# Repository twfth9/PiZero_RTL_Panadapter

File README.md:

# PiZero_RTL_Panadapter
Rasp Pi Zero, RTLSDR-based panadapter module

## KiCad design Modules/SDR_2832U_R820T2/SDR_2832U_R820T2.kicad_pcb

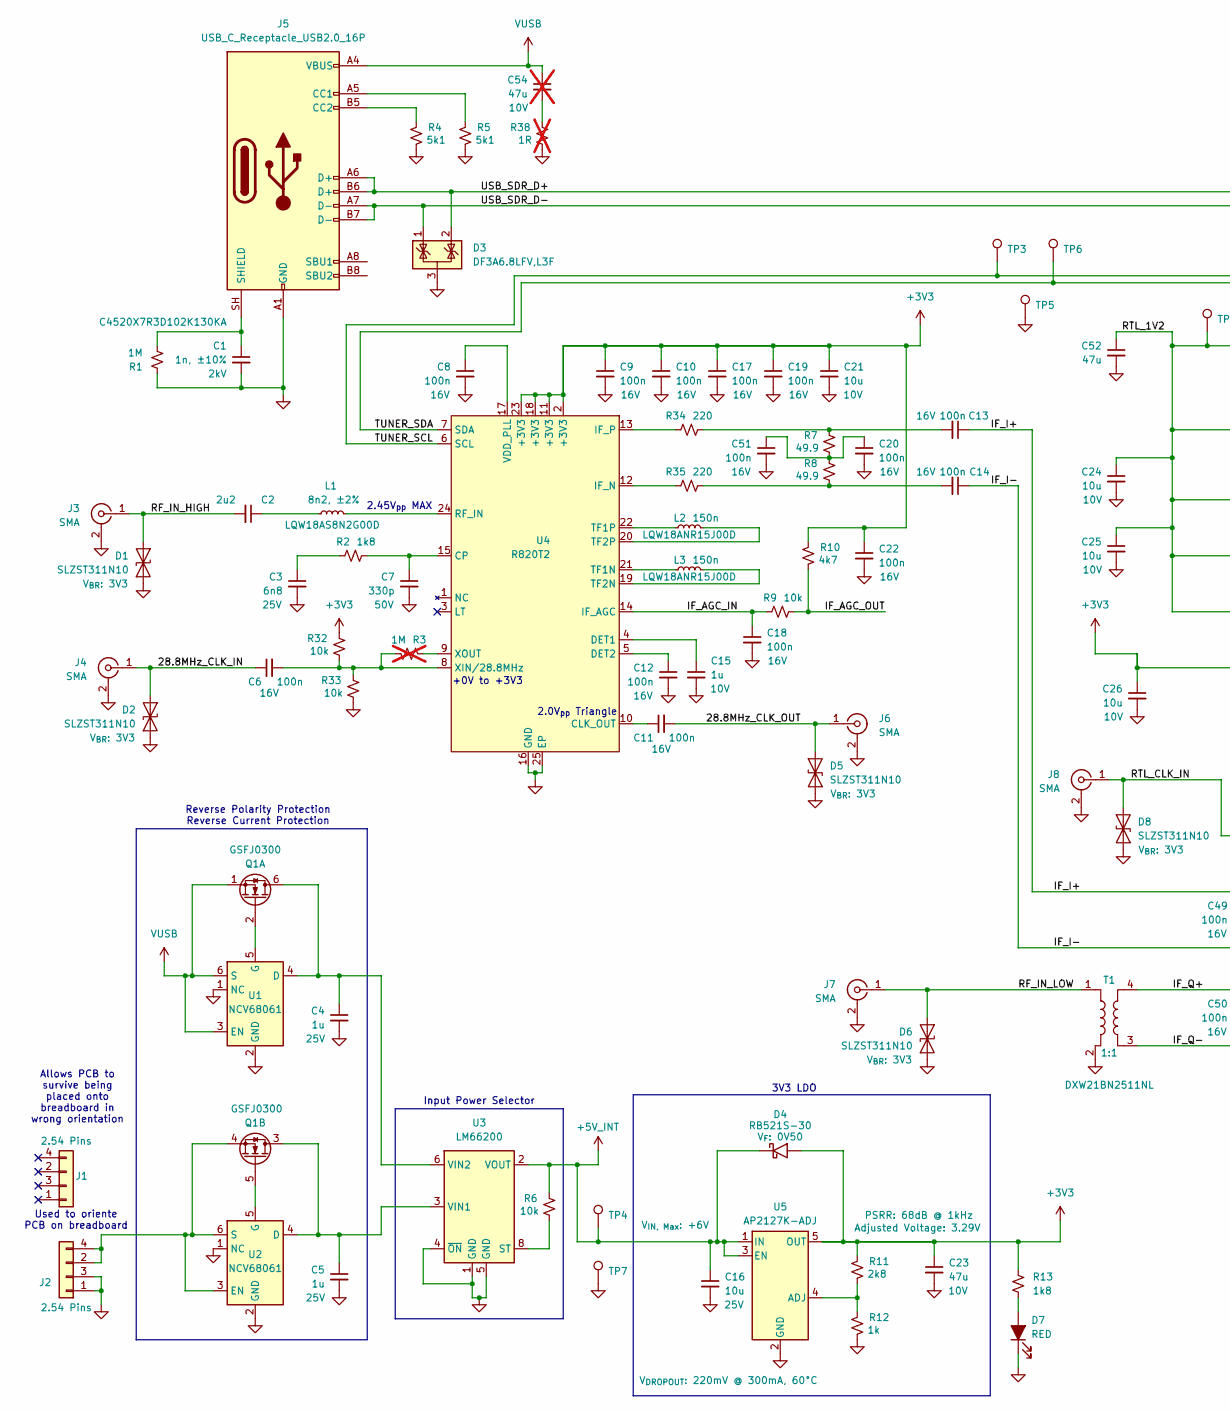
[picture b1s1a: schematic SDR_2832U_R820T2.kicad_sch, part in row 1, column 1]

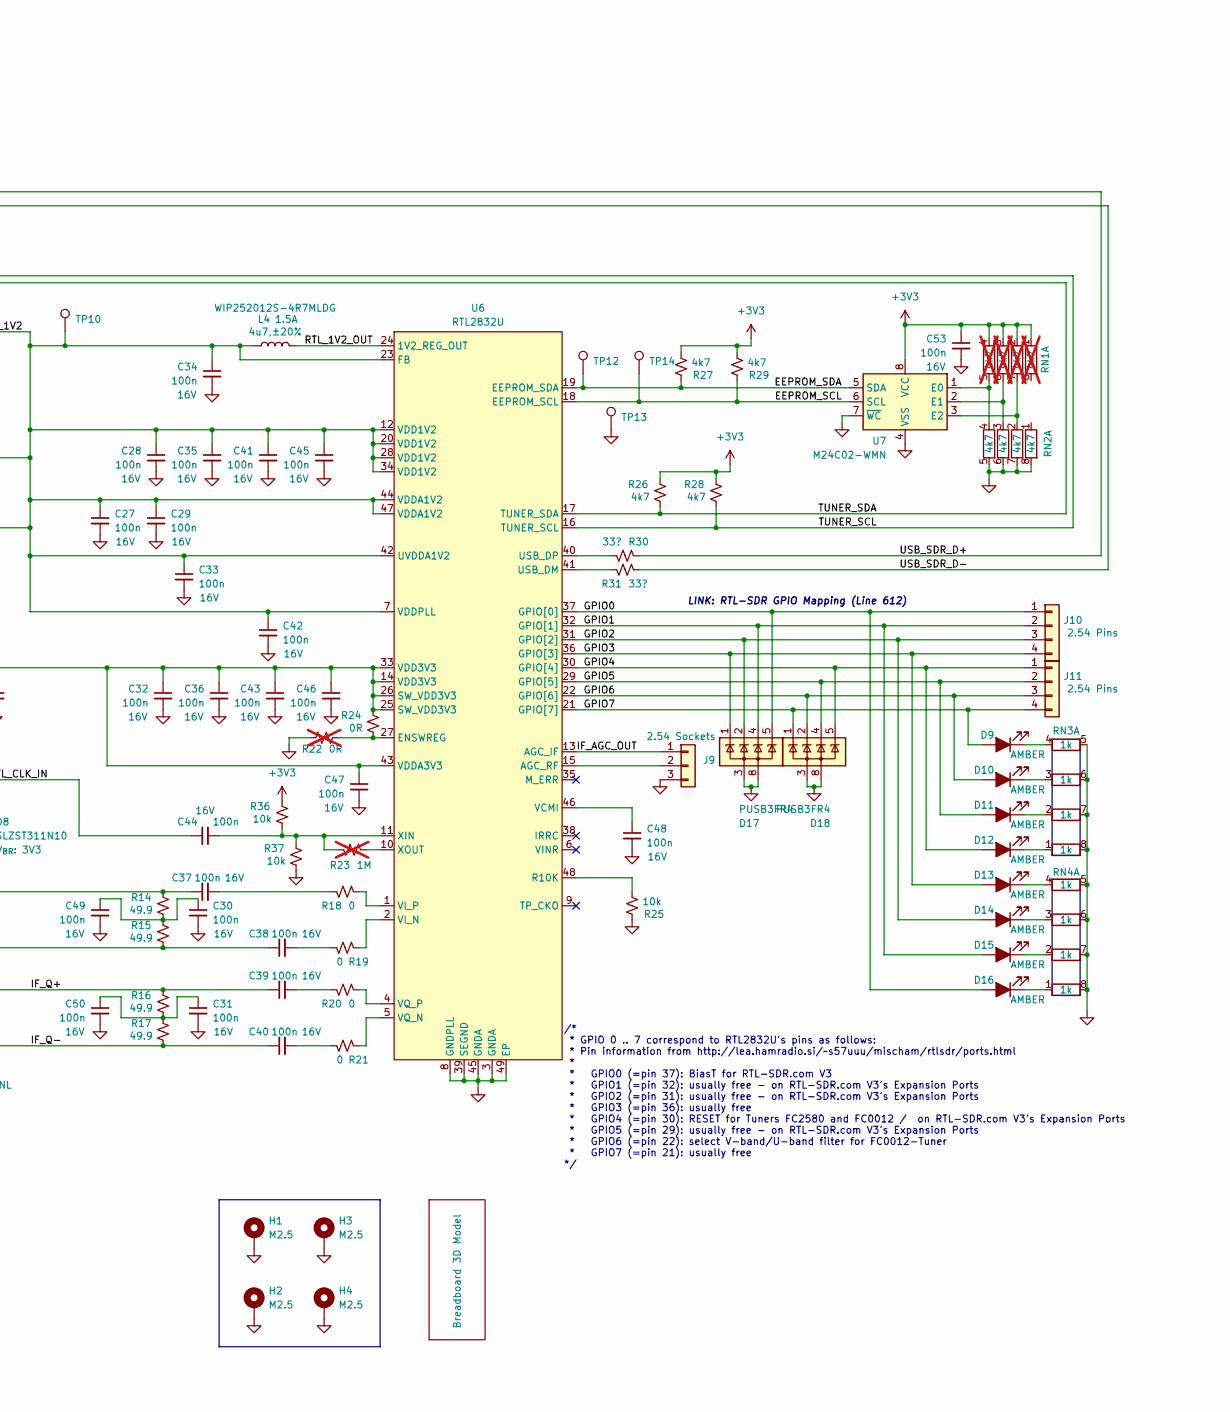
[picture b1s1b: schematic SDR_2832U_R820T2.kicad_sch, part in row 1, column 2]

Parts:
C1: 1n, ±10%; C_1808_4520Metric; Voltage 2kV; Part Number C4520X7R3D102K130KA; DigiKey 445-2386-1-ND
C2: 2u2; Worthington_C_Narrow_0402_0603; Voltage 10V
C3: 6n8; Worthington_C_Narrow_0201; Voltage 25V; Manufacturer Part Number GMC02X5R682K25NT; DigiKey 4713-GMC02X5R682K25NTCT-ND
C4, C5: 1u; Worthington_C_Narrow_0402; Voltage 25V; Manufacturer Part Number GMC04X5R106M10NT; DigiKey 4713-GMC04X5R106M10NTCT-ND
C6, C8, C9, C10, C11, C12, C13, C14, C17, C18, C19, C20, C22, C27, C28, C29, C30, C31, C32, C33, C34, C35, C36, C37, C38, C39, C40, C41, C42, C43, C44, C45, C46, C47, C48, C49, C50, C51, C53: 100n; Worthington_C_Narrow_0201; Voltage 16V; Manufacturer Part Number C0603X6S1C104K030BC; DigiKey 445-15903-1-ND
C7: 330p; Worthington_C_Narrow_0201; Voltage 50V; Manufacturer Part Number GMC02X7R331J50NT; DigiKey 4713-GMC02X7R331J50NTCT-ND
C15: 1u; Worthington_C_Narrow_0201; Voltage 10V; Manufacturer Part Number GMC02X5R105K10NT; DigiKey 4713-GMC02X5R105K10NTCT-ND
C16: 10u; Worthington_C_Narrow_0402; Voltage 25V; Manufacturer Part Number GMC04X5R106M10NT; DigiKey 4713-GMC04X5R106M10NTCT-ND
C21, C24, C25, C26: 10u; Worthington_C_Narrow_0402; Voltage 10V; Manufacturer Part Number GMC04X5R106M10NT; DigiKey 4713-GMC04X5R106M10NTCT-ND
C23: 47u; Worthington_C_0805; Voltage 10V; Manufacturer Part Number GMC04X5R106M10NT; DigiKey 4713-GMC04X5R106M10NTCT-ND
C52: 47u; Worthington_C_Narrow_0603
C54: 47u; Worthington_C_0805; Voltage 10V; Manufacturer Part Number GMC04X5R106M10NT; DigiKey 4713-GMC04X5R106M10NTCT-ND; not fitted
D1, D2, D5, D6, D8: SLZST311N10; D_SOD-882; Part Number SLZST311N10; DigiKey 5399-SLZST311N10CT-ND
D3: DF3A6.8LFV,L3F; SOT-723
D4: RB521S-30; D_SOD-523; Part Number RB521S-30; DigiKey 5399-RB521S-30CT-ND
D7: RED; Worthington_LED_0402
D9, D10, D11, D12, D13, D14, D15, D16: AMBER; Worthington_LED_0402
D17, D18: PUSB3FR4; Diodes_UDFN-10_1x2.5mm_P0.5mm
H1, H2, H3, H4: M2.5; MountingHole_2.7mm_M2.5_ISO7380_Pad
J1, J2: 2.54 Pins; PinHeader_2x02_P2.54mm_Vertical
J3, J4, J6, J7, J8: SMA; SMA_Amphenol_132289_EdgeMount
J5: USB_C_Receptacle_USB2.0_16P; USB_C_Receptacle_GCT_USB4105-xx-A_16P_TopMnt_Horizontal
J9: 2.54 Sockets; PinHeader_1x03_P2.54mm_Vertical
J10, J11: 2.54 Pins; PinHeader_1x04_P2.54mm_Vertical
L1: 8n2, ±2%; Worthington_L_Narrow_0603_RF; Manufacturer Part Number LQW18AS8N2G00D; DigiKey 490-LQW18AS8N2G00DCT-ND
L2, L3: 150n; Worthington_L_Narrow_0603_RF; Manufacturer Part Number LQW18ANR15J00D; DigiKey 490-6924-1-ND
L4: 4u7,±20%; L_1008_2520Metric; Manufacturer Part Number WIP252012S-4R7MLDG; DigiKey 3526-WIP252012S-4R7MLDGCT-ND
Q1: GSFJ0300; SOT-563; Part Number GSFJ0300; DigiKey 4786-GSFJ0300CT-ND
R1: 1M; Worthington_R_Narrow_0201
R2, R13: 1k8; Worthington_R_Narrow_0201
R3, R23: 1M; Worthington_R_Narrow_0201; not fitted
R4, R5: 5k1; Worthington_R_Narrow_0201
R6, R9, R25, R32, R33, R36, R37: 10k; Worthington_R_Narrow_0201
R7, R8, R14, R15, R16, R17: 49.9; Worthington_R_Narrow_0201
R10, R26, R27, R28, R29: 4k7; Worthington_R_Narrow_0201
R11: 2k8; Worthington_R_Narrow_0201
R12: 1k; Worthington_R_Narrow_0201
R18, R19, R20, R21: 0; Worthington_R_Narrow_0201
R22: 0R; Worthington_R_Narrow_0201; not fitted
R24: 0R; Worthington_R_Narrow_0201
R30, R31: 33?; Worthington_R_Narrow_0201
R34, R35: 220; Worthington_R_Narrow_0201
R38: 1R; R_0805_2012Metric; not fitted
RN1: 4k7; RESCAXE80P320X160X70-8N; DigiKey Part CAT16-4702F4LFCT-ND; not fitted
RN2: 4k7; RESCAXE80P320X160X70-8N; DigiKey Part CAT16-4702F4LFCT-ND
RN3, RN4: 1k; RESCAXE80P320X160X70-8N; DigiKey Part CAT16-4702F4LFCT-ND
S1: Breadboard 3D Model; Breadboard_400
T1: DXW21BN2511NL; XFMR_ATB2012-50011-T000
TP3, TP4, TP5, TP6, TP7, TP10, TP12, TP13, TP14: TestPoint; TestPoint_Keystone_5000-5004_Miniature
U1, U2: NCV68061; TSOP-6_1.65x3.05mm_P0.95mm; DigiKey 488-NCV68061SNAIT1GCT-ND
U3: LM66200; SOT-583-8
U4: R820T2; QFN-24-1EP_4x4mm_P0.5mm_EP2.15x2.15mm_ThermalVias
U5: AP2127K-ADJ; SOT-23-5; Adjusted Voltage 3.29V; Part Number AP2127K-ADJTRG1; DigiKey AP2127K-ADJTRG1DICT-ND
U6: RTL2832U; QFN-48-1EP_6x6mm_P0.4mm_EP4.2x4.2mm_ThermalVias
U7: M24C02-WMN; SOIC-8_3.9x4.9mm_P1.27mm

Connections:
+3V3: C9.1, C10.1, C17.1, C19.1, C21.1, C22.1, C23.1, C26.1, C32.1, C36.1, C43.1, C46.1, C47.1, C53.1, D4.2 (A), R10.2, R11.2, R13.1, R24.2, R26.2, R27.1, R28.2, R29.1, R32.2, R36.2, RN1.1 (4), RN1.2, RN1.3, RN1.4, U4.2 (+3V3), U4.11 (+3V3), U4.18 (+3V3), U4.23 (+3V3), U5.5 (OUT), U6.14 (VDD3V3), U6.25 (SW_VDD3V3), U6.26 (SW_VDD3V3), U6.33 (VDD3V3), U6.43 (VDDA3V3), U7.8 (VCC)
+5V_INT: C16.1, D4.1 (K), R6.2, TP4.1 (1_1), U3.2 (VOUT), U3.7 (VOUT), U5.1 (IN), U5.3 (EN)
/28.8MHz_CLK_IN: C6.1, D2.2 (A2), J4.1 (In)
/28.8MHz_CLK_OUT: C11.2, D5.2 (A2), J6.1 (In)
/EEPROM_SCL: R29.2, TP14.1 (1_1), U6.18 (EEPROM_SCL), U7.6 (SCL)
/EEPROM_SDA: R27.2, TP12.1 (1_1), U6.19 (EEPROM_SDA), U7.5 (SDA)
/GPIO0: D16.2 (A), D17.5 (K), J10.1, U6.37 (GPIO[0])
/GPIO1: D15.2 (A), D17.4 (K), J10.2, U6.32 (GPIO[1])
/GPIO2: D14.2 (A), D17.2 (K), J10.3, U6.31 (GPIO[2])
/GPIO3: D13.2 (A), D17.1 (K), J10.4, U6.36 (GPIO[3])
/GPIO4: D12.2 (A), D18.5 (K), J11.1, U6.30 (GPIO[4])
/GPIO5: D11.2 (A), D18.4 (K), J11.2, U6.29 (GPIO[5])
/GPIO6: D10.2 (A), D18.2 (K), J11.3, U6.22 (GPIO[6])
/GPIO7: D9.2 (A), D18.1 (K), J11.4, U6.21 (GPIO[7])
/IF_AGC_IN: C18.1, R9.1, U4.14 (IF_AGC)
/IF_AGC_OUT: J9.1, R9.2, R10.1, U6.13 (AGC_IF)
/IF_I+: C13.1, C37.1, R14.2
/IF_I-: C14.1, C38.1, R15.1
/IF_Q+: C39.1, R16.2, T1.4
/IF_Q-: C40.1, R17.1, T1.3
/RF_IN_HIGH: C2.2, D1.2 (A2), J3.1 (In)
/RF_IN_LOW: D6.2 (A2), J7.1 (In), T1.1
/RTL_1V2: C24.1, C25.1, C27.1, C28.1, C29.1, C33.1, C34.1, C35.1, C41.1, C42.1, C45.1, C52.1, L4.2, TP10.1 (1_1), U6.7 (VDDPLL), U6.12 (VDD1V2), U6.20 (VDD1V2), U6.23 (FB), U6.28 (VDD1V2), U6.34 (VDD1V2), U6.42 (UVDDA1V2), U6.44 (VDDA1V2), U6.47 (VDDA1V2)
/RTL_1V2_OUT: L4.1, U6.24 (1V2_REG_OUT)
/RTL_CLK_IN: C44.1, D8.2 (A2), J8.1 (In)
/TUNER_SCL: R28.1, TP3.1 (1_1), U4.6 (SCL), U6.16 (TUNER_SCL)
/TUNER_SDA: R26.1, TP6.1 (1_1), U4.7 (SDA), U6.17 (TUNER_SDA)
/USB_SDR_D+: D3.2 (K), J5.A6 (D+), J5.B6 (D+), R30.1
/USB_SDR_D-: D3.1 (K), J5.A7 (D-), J5.B7 (D-), R31.2
GND: C1.2, C3.2, C4.2, C5.2, C7.2, C8.2, C9.2, C10.2, C12.2, C15.2, C16.2, C17.2, C18.2, C19.2, C20.2, C21.2, C22.2, C23.2, C24.2, C25.2, C26.2, C27.2, C28.2, C29.2, C30.2, C31.2, C32.2, C33.2, C34.2, C35.2, C36.2, C41.2, C42.2, C43.2, C45.2, C46.2, C47.2, C48.2, C49.2, C50.2, C51.2, C52.2, C53.2, D1.1 (A1), D2.1 (A1), D3.3 (A), D5.1 (A1), D6.1 (A1), D7.1 (K), D8.1 (A1), D17.3 (A), D17.8 (A), D18.3 (A), D18.8 (A), H1.1 (1_1), H2.1 (1_1), H3.1 (1_1), H4.1 (1_1), J2.1, J2.3, J3.2 (Ext), J4.2 (Ext), J5.A1 (GND), J5.A12 (GND), J5.B1 (GND), J5.B12 (GND), J6.2 (Ext), J7.2 (Ext), J8.2 (Ext), J9.3, R1.1, R4.1, R5.1, R12.1, R22.2, R25.2, R33.1, R37.1, R38.1, RN2.5, RN2.6, RN2.7 (5), RN2.8, RN3.5, RN3.6, RN3.7 (5), RN3.8, RN4.5, RN4.6, RN4.7 (5), RN4.8, T1.2, TP5.1 (1_1), TP7.1 (1_1), TP13.1 (1_1), U1.1 (NC), U1.2 (GND), U2.1 (NC), U2.2 (GND), U3.1 (GND), U3.4 (~ON), U3.5 (GND), U4.16 (GND), U4.25 (EP), U5.2 (GND), U6.3 (GNDA), U6.8 (GNDPLL), U6.39 (SEGND), U6.45 (GNDA), U6.49 (EP), U7.4 (VSS), U7.7 (~WC); also elsewhere on the board
unnamed: C2.1, L1.1
unnamed: C3.1, R2.1
unnamed: C13.2, R7.2, R34.2
unnamed: C14.2, R8.1, R35.2
unnamed: C20.1, C51.1, R7.1, R8.2
unnamed: C30.1, C49.1, R14.1, R15.2
unnamed: C31.1, C50.1, R16.1, R17.2
unnamed: C37.2, R18.1
unnamed: C38.2, R19.1
unnamed: C39.2, R20.1
unnamed: C40.2, R21.1
unnamed: C54.2, R38.2
unnamed: D7.2 (A), R13.2
unnamed: D9.1 (K), RN3.4
unnamed: D10.1 (K), RN3.3
unnamed: D11.1 (K), RN3.2
unnamed: D12.1 (K), RN3.1 (4)
unnamed: D13.1 (K), RN4.4
unnamed: D14.1 (K), RN4.3
unnamed: D15.1 (K), RN4.2
unnamed: D16.1 (K), RN4.1 (4)
unnamed: J2.2, J2.4, Q1.4 (S), U2.3 (EN), U2.6 (S)
unnamed: J5.A5 (CC1), R5.2
unnamed: J5.B5 (CC2), R4.2
unnamed: C1.1, J5.SH (SHIELD), R1.2
unnamed: J9.2, U6.15 (AGC_RF)
unnamed: C4.1, Q1.6 (D), U1.4 (D), U3.6 (VIN2)
unnamed: Q1.2 (G), U1.5 (G)
unnamed: C5.1, Q1.3 (D), U2.4 (D), U3.3 (VIN1)
unnamed: Q1.5 (G), U2.5 (G)
unnamed: RN1.7 (5), RN2.2, U7.3 (E2)
unnamed: R6.1, U3.8 (ST)
unnamed: C11.1, U4.10 (CLK_OUT)
unnamed: C7.1, R2.2, U4.15 (CP)
unnamed: C15.1, U4.4 (DET1)
unnamed: C12.1, U4.5 (DET2)
unnamed: R35.1, U4.12 (IF_N)
unnamed: R34.1, U4.13 (IF_P)
unnamed: L1.2, U4.24 (RF_IN)
unnamed: L3.1, U4.21 (TF1N)
unnamed: L2.1, U4.22 (TF1P)
unnamed: L3.2, U4.19 (TF2N)
unnamed: L2.2, U4.20 (TF2P)
unnamed: C8.1, U4.17 (VDD_PLL)
unnamed: C6.2, R3.2, R32.1, R33.2, U4.8 (XIN/28.8MHz)
unnamed: R3.1, U4.9 (XOUT)
unnamed: R11.1, R12.2, U5.4 (ADJ)
unnamed: R22.1, R24.1, U6.27 (ENSWREG)
unnamed: R25.1, U6.48 (R10K)
unnamed: R31.1, U6.41 (USB_DM)
unnamed: R30.2, U6.40 (USB_DP)
unnamed: C48.1, U6.46 (VCMI)
unnamed: R19.2, U6.2 (VI_N)
unnamed: R18.2, U6.1 (VI_P)
unnamed: R21.2, U6.5 (VQ_N)
unnamed: R20.2, U6.4 (VQ_P)
unnamed: C44.2, R23.1, R36.1, R37.2, U6.11 (XIN)
unnamed: R23.2, U6.10 (XOUT)
unnamed: RN1.5, RN2.4, U7.1 (E0)
unnamed: RN1.6, RN2.3, U7.2 (E1)
VUSB: C54.1, J5.A4 (VBUS), J5.A9 (VBUS), J5.B4 (VBUS), J5.B9 (VBUS), Q1.1 (S), U1.3 (EN), U1.6 (S)

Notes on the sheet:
Used to oriente PCB on breadboard
Allows PCB to survive being placed onto breadboard in wrong orientation
2.45V_{pp} MAX
/* * GPIO 0 .. 7 correspond to RTL2832U's pins as follows: * Pin information from http://lea.hamradio.si/~s57uuu/mischam/rtlsdr/ports.html * * GPIO0 (=pin 37): BiasT for RTL-SDR.com V3 * GPIO1 (=pin 32): usually free - on RTL-SDR.com V3's Expansion Ports * GPIO2 (=pin 31): usually free - on RTL-SDR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
+0V to +3V3
3V3 LDO
Input Power Selector
Reverse Polarity Protection Reverse Current Protection
LINK: RTL-SDR GPIO Mapping (Line 612)
2.0V_{pp} Triangle

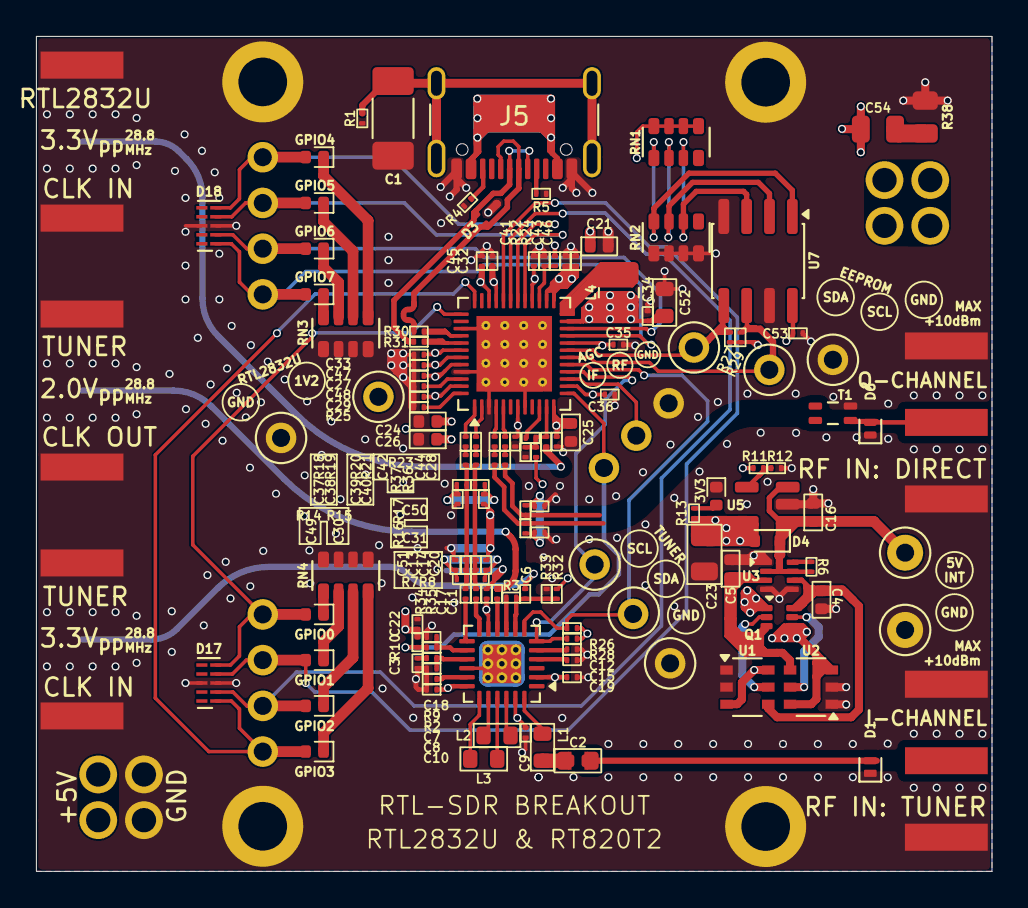
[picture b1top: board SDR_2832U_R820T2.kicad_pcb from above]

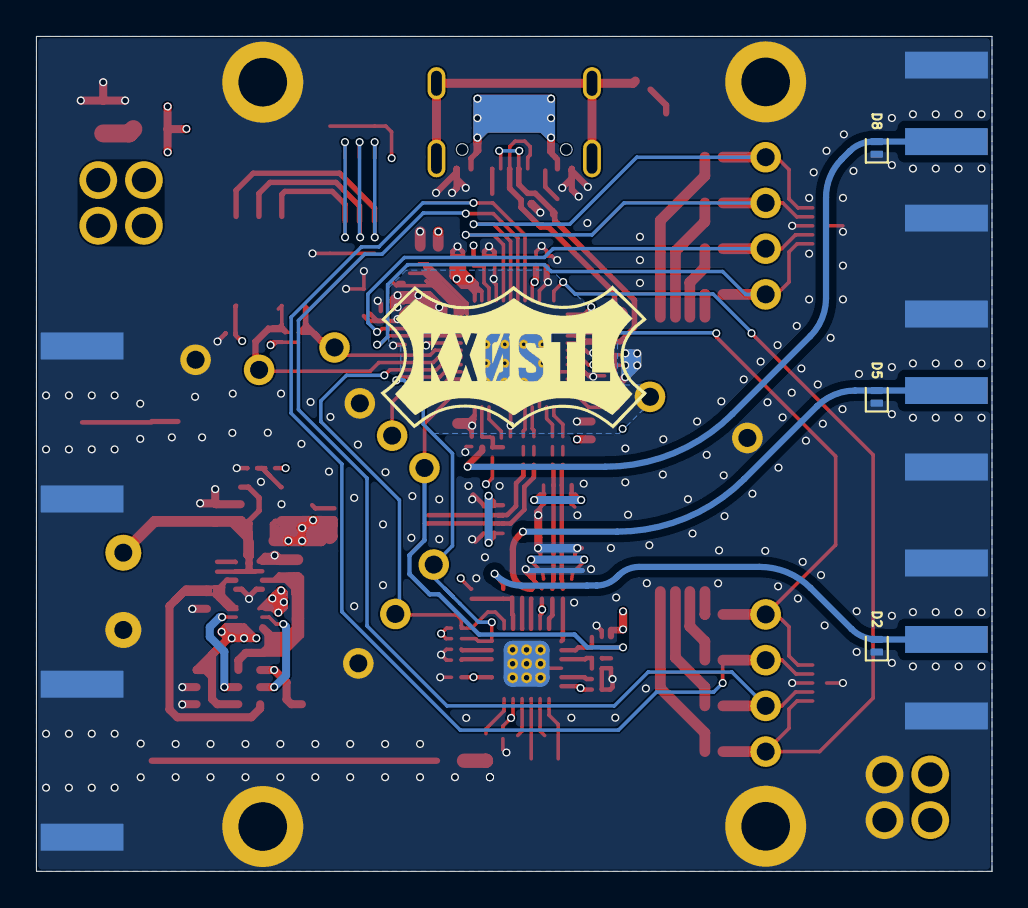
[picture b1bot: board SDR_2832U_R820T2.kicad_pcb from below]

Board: 4 copper layers, 53.1 x 46.4 mm, 153 parts (8 on the bottom side), 91 nets.

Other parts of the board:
TP11: TestPoint; TestPoint_Keystone_5000-5004_Miniature

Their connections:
GND: TP11.1 (1_1); also elsewhere on the board

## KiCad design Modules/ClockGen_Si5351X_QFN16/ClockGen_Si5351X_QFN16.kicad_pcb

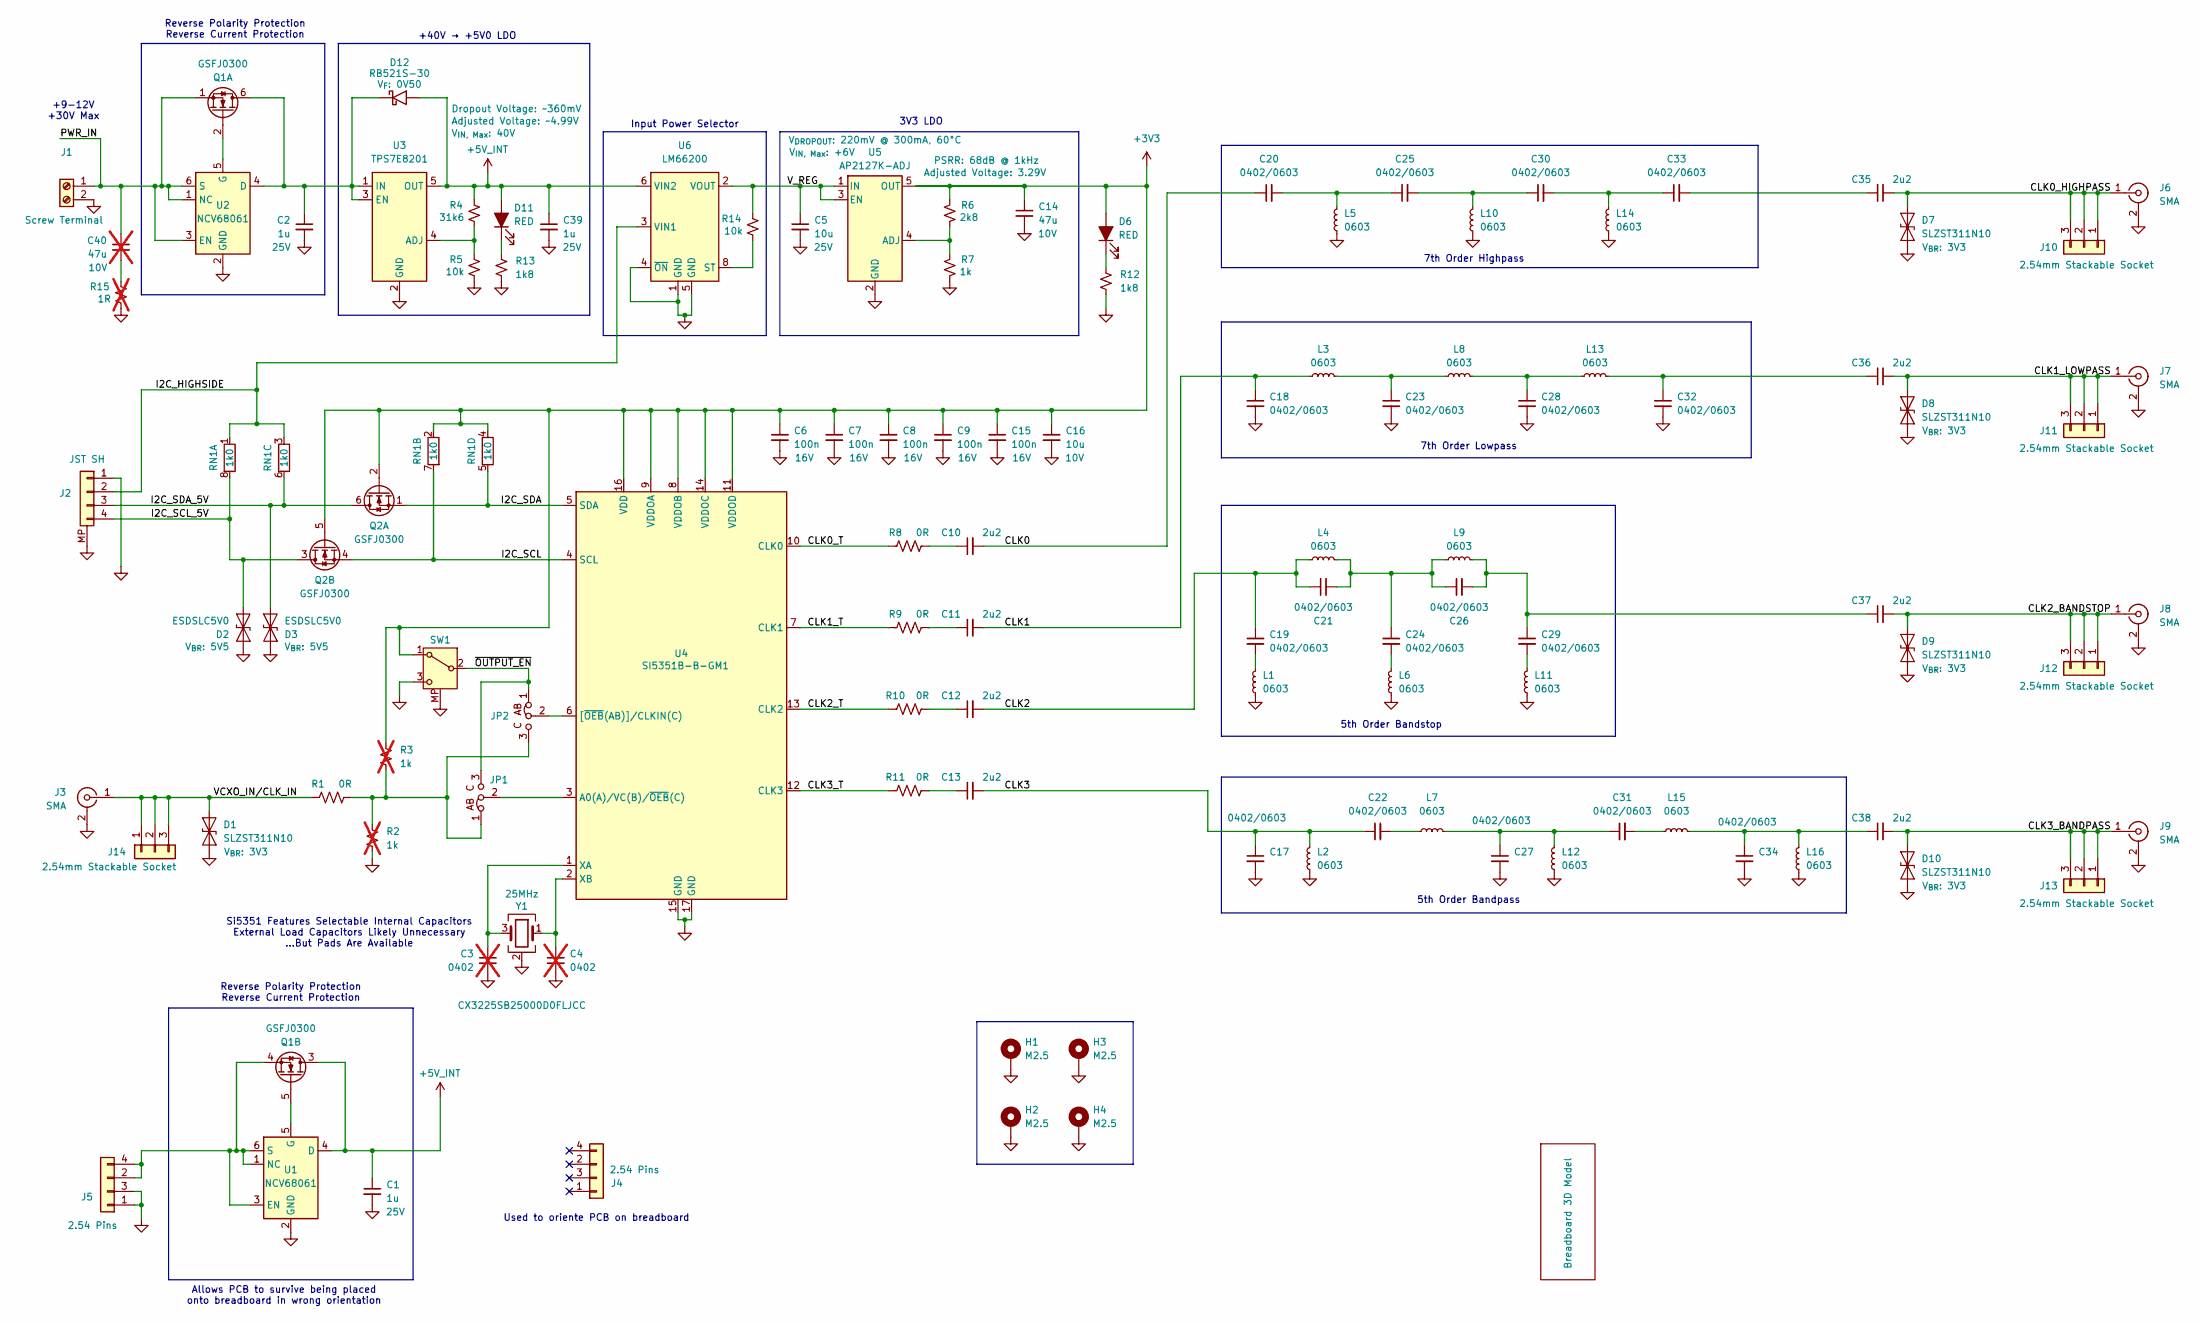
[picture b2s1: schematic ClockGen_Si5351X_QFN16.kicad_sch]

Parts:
C1, C2, C39: 1u; Worthington_C_Narrow_0402; Voltage 25V; Manufacturer Part Number GMC04X5R106M10NT; DigiKey 4713-GMC04X5R106M10NTCT-ND
C3, C4: 0402; Worthington_C_Narrow_0402; not fitted
C5: 10u; Worthington_C_Narrow_0402; Voltage 25V; Manufacturer Part Number GMC04X5R106M10NT; DigiKey 4713-GMC04X5R106M10NTCT-ND
C6, C7, C8, C9, C15: 100n; Worthington_C_Narrow_0201; Voltage 16V; Manufacturer Part Number C0603X6S1C104K030BC; DigiKey 445-15903-1-ND
C10, C11, C12, C13: 2u2; Worthington_C_Narrow_0402; Voltage 10V
C14: 47u; Worthington_C_0805; Voltage 10V; Manufacturer Part Number GMC04X5R106M10NT; DigiKey 4713-GMC04X5R106M10NTCT-ND
C16: 10u; Worthington_C_Narrow_0402; Voltage 10V; Manufacturer Part Number GMC04X5R106M10NT; DigiKey 4713-GMC04X5R106M10NTCT-ND
C17, C18, C19, C20, C21, C22, C23, C24, C25, C26, C27, C28, C29, C30, C31, C32, C33, C34: 0402/0603; Worthington_C_Narrow_0402_0603
C35, C36, C37, C38: 2u2; Worthington_C_Narrow_0402_0603; Voltage 10V
C40: 47u; Worthington_C_0805; Voltage 10V; Manufacturer Part Number GMC04X5R106M10NT; DigiKey 4713-GMC04X5R106M10NTCT-ND; not fitted
D1, D7, D8, D9, D10: SLZST311N10; D_SOD-882; Part Number SLZST311N10; DigiKey 5399-SLZST311N10CT-ND
D2, D3: ESDSLC5V0; D_SOD-882; Part Number 353-ESDSLC5V0L2B-TPCT-ND; DigiKey ESDSLC5V0L2B-TP
D6, D11: RED; Worthington_LED_0402
D12: RB521S-30; D_SOD-523; Part Number RB521S-30; DigiKey 5399-RB521S-30CT-ND
H1, H2, H3, H4: M2.5; MountingHole_2.7mm_M2.5_ISO7380_Pad
J1: Screw Terminal; TerminalBlock_Phoenix_MPT-0,5-2-2.54_1x02_P2.54mm_Horizontal; Part Number 1725656; DigiKey 277-1273-ND
J2: JST SH; JST_SH_SM04B-SRSS-TB_1x04-1MP_P1.00mm_Horizontal
J3, J6, J7, J8, J9: SMA; SMA_Molex_73251-2200_Horizontal
J4, J5: 2.54 Pins; PinHeader_2x02_P2.54mm_Vertical
J10, J11, J12, J13, J14: 2.54mm Stackable Socket; PinSocket_1x03_P2.54mm_Vertical
JP1, JP2: Jumper_3_Bridged12; SolderJumper-3_P2.0mm_Open_TrianglePad1.0x1.5mm
L1, L2, L3, L4, L5, L6, L7, L8, L9, L10, L11, L12, L13, L14, L15, L16: 0603; Worthington_L_Narrow_0603_RF
Q1, Q2: GSFJ0300; SOT-563; Part Number GSFJ0300; DigiKey 4786-GSFJ0300CT-ND
R1, R8, R9, R10, R11: 0R; Worthington_R_Narrow_0402
R2, R3: 1k; Worthington_R_Narrow_0402; not fitted
R4: 31k6; Worthington_R_Narrow_0201
R5, R14: 10k; Worthington_R_Narrow_0201
R6: 2k8; Worthington_R_Narrow_0201
R7: 1k; Worthington_R_Narrow_0201
R12, R13: 1k8; Worthington_R_Narrow_0201
R15: 1R; R_0805_2012Metric; not fitted
RN1: 1k0; RESCAXE80P320X160X70-8N; DigiKey Part CAT16-4702F4LFCT-ND
S1: Breadboard 3D Model; Breadboard_400
SW1: SW_SPDT; SW_Slide_SPDT_Straight_CK_OS102011MS2Q
U1, U2: NCV68061; TSOP-6_1.65x3.05mm_P0.95mm; DigiKey 488-NCV68061SNAIT1GCT-ND
U3: TPS7E8201; SOT-23-5; Adjusted Voltage ~4.99V; Dropout Voltage ~360mV
U4: SI5351B-B-GM1; QFN-16-1EP_3x3mm_P0.5mm_EP1.9x1.9mm_ThermalVias
U5: AP2127K-ADJ; SOT-23-5; Adjusted Voltage 3.29V; Part Number AP2127K-ADJTRG1; DigiKey AP2127K-ADJTRG1DICT-ND
U6: LM66200; SOT-583-8
Y1: 25MHz; Crystal_SMD_Kyocera_CX3225SB-4Pin_3.2x2.5mm

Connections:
+3V3: C6.1, C7.1, C8.1, C9.1, C14.1, C15.1, C16.1, D6.2 (A), Q2.2 (G), Q2.5 (G), R3.1, R6.2, RN1.2, RN1.4, SW1.1 (A), U4.8 (VDDOB), U4.9 (VDDOA), U4.11 (VDDOD), U4.14 (VDDOC), U4.16 (VDD), U5.5 (OUT)
+5V_INT: C1.1, C39.1, D11.2 (A), D12.2 (A), Q1.3 (D), R4.2, U1.4 (D), U3.5 (OUT), U6.6 (VIN2)
/CLK0: C10.2, C20.1
/CLK0_HIGHPASS: C35.2, D7.2 (A2), J6.1 (In), J10.1, J10.2, J10.3
/CLK0_T: R8.1, U4.10 (CLK0)
/CLK1: C11.2, C18.1, L3.1
/CLK1_LOWPASS: C36.2, D8.2 (A2), J7.1 (In), J11.1, J11.2, J11.3
/CLK1_T: R9.1, U4.7 (CLK1)
/CLK2: C12.2, C19.1, C21.1, L4.1
/CLK2_BANDSTOP: C37.2, D9.2 (A2), J8.1 (In), J12.1, J12.2, J12.3
/CLK2_T: R10.1, U4.13 (CLK2)
/CLK3: C13.2, C17.1, C22.1, L2.2
/CLK3_BANDPASS: C38.2, D10.2 (A2), J9.1 (In), J13.1, J13.2, J13.3
/CLK3_T: R11.1, U4.12 (CLK3)
/I2C_HIGHSIDE: J2.2, RN1.1 (4), RN1.3, U6.3 (VIN1)
/I2C_SCL: Q2.4 (S), RN1.7 (5), U4.4 (SCL)
/I2C_SCL_5V: D2.1 (A1), J2.4, Q2.3 (D), RN1.8
/I2C_SDA: Q2.1 (S), RN1.5, U4.5 (SDA)
/I2C_SDA_5V: D3.2 (A2), J2.3, Q2.6 (D), RN1.6
/PWR_IN: C40.1, J1.1, Q1.1 (S), U2.1 (NC), U2.3 (EN), U2.6 (S)
/VCXO_IN/CLK_IN: D1.2 (A2), J3.1 (In), J14.1, J14.2, J14.3, R1.1
/V_REG: C5.1, R14.2, U5.1 (IN), U5.3 (EN), U6.2 (VOUT), U6.7 (VOUT)
/~OUTPUT_EN: JP1.3 (B), JP2.1 (A), SW1.2 (B)
GND: C1.2, C2.2, C3.2, C4.2, C5.2, C6.2, C7.2, C8.2, C9.2, C14.2, C15.2, C16.2, C17.2, C18.2, C23.2, C27.2, C28.2, C32.2, C34.2, C39.2, D1.1 (A1), D2.2 (A2), D3.1 (A1), D7.1 (A1), D8.1 (A1), D9.1 (A1), D10.1 (A1), H1.1 (1_1), H2.1 (1_1), H3.1 (1_1), H4.1 (1_1), J1.2, J2.1, J2.MP, J3.2 (Ext), J5.1, J5.3, J6.2 (Ext), J7.2 (Ext), J8.2 (Ext), J9.2 (Ext), L1.1, L2.1, L5.1, L6.1, L10.1, L11.1, L12.1, L14.1, L16.1, R2.2, R5.1, R7.1, R12.2, R13.2, R15.1, SW1.3 (C), SW1.MP, U1.2 (GND), U2.2 (GND), U3.2 (GND), U4.15 (GND), U4.17 (GND), U5.2 (GND), U6.1 (GND), U6.4 (~ON), U6.5 (GND), Y1.2 (G), Y1.4 (G)
unnamed: C10.1, R8.2
unnamed: C11.1, R9.2
unnamed: C12.1, R10.2
unnamed: C13.1, R11.2
unnamed: C19.2, L1.2
unnamed: C20.2, C25.1, L5.2
unnamed: C21.2, C24.1, C26.1, L4.2, L9.1
unnamed: C22.2, L7.1
unnamed: C23.1, L3.2, L8.1
unnamed: C24.2, L6.2
unnamed: C25.2, C30.1, L10.2
unnamed: C26.2, C29.1, C37.1, L9.2
unnamed: C27.1, C31.1, L7.2, L12.2
unnamed: C28.1, L8.2, L13.1
unnamed: C29.2, L11.2
unnamed: C30.2, C33.1, L14.2
unnamed: C31.2, L15.1
unnamed: C32.1, C36.1, L13.2
unnamed: C33.2, C35.1
unnamed: C34.1, C38.1, L15.2, L16.2
unnamed: C40.2, R15.2
unnamed: D6.1 (K), R12.1
unnamed: D11.1 (K), R13.1
unnamed: C2.1, D12.1 (K), Q1.6 (D), U2.4 (D), U3.1 (IN), U3.3 (EN)
unnamed: J5.2, J5.4, Q1.4 (S), U1.1 (NC), U1.3 (EN), U1.6 (S)
unnamed: JP1.1 (A), JP2.3 (B), R1.2, R2.1, R3.2
unnamed: JP1.2 (C), U4.3 (A0(A)/VC(B)/~OEB(C))
unnamed: JP2.2 (C), U4.6 ([~OEB(AB)]/CLKIN(C))
unnamed: Q1.2 (G), U2.5 (G)
unnamed: Q1.5 (G), U1.5 (G)
unnamed: R4.1, R5.2, U3.4 (ADJ)
unnamed: C3.1, U4.1 (XA), Y1.3
unnamed: C4.1, U4.2 (XB), Y1.1
unnamed: R6.1, R7.2, U5.4 (ADJ)
unnamed: R14.1, U6.8 (ST)

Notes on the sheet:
7th Order Lowpass
5th Order Bandpass
Used to oriente PCB on breadboard
Reverse Polarity Protection Reverse Current Protection
5th Order Bandstop
Allows PCB to survive being placed onto breadboard in wrong orientation
+9-12V +30V Max
Input Power Selector
Si5351 Features Selectable Internal Capacitors External Load Capacitors Likely Unnecessary ...But Pads Are Available
7th Order Highpass
3V3 LDO
+40V → +5V0 LDO

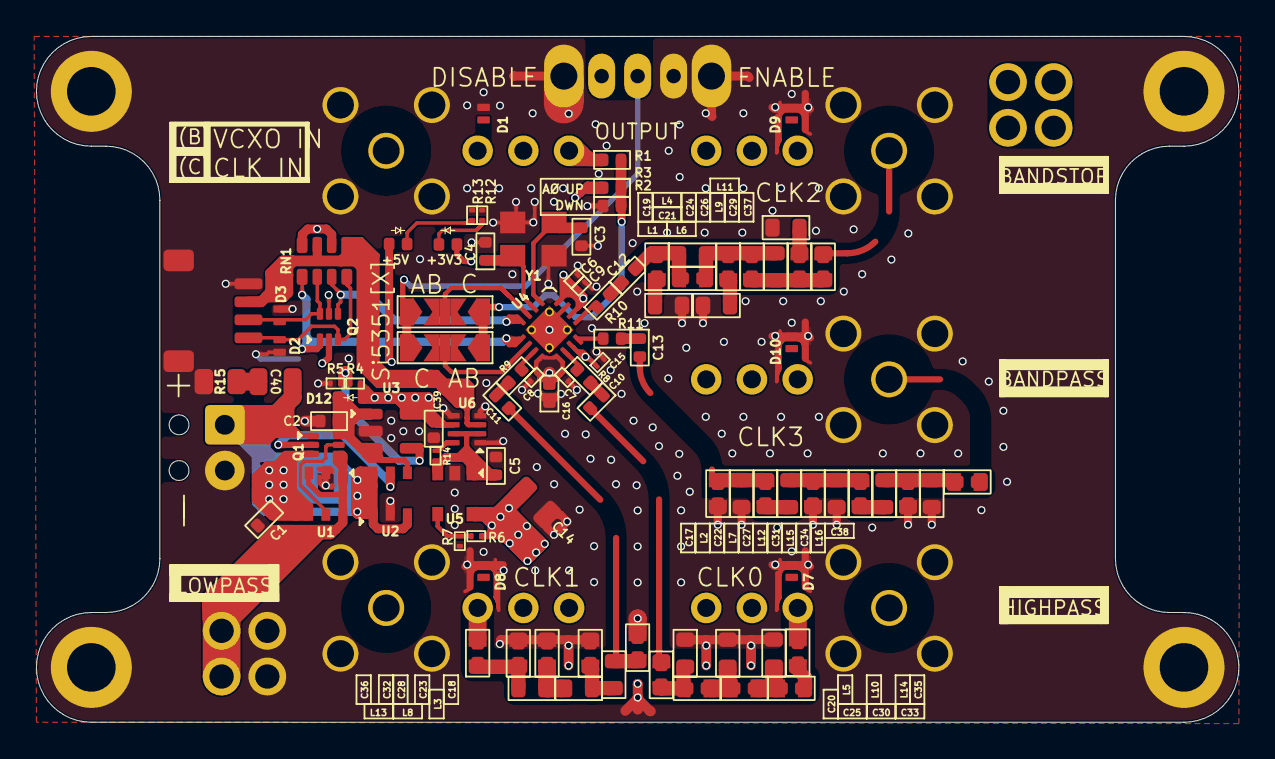
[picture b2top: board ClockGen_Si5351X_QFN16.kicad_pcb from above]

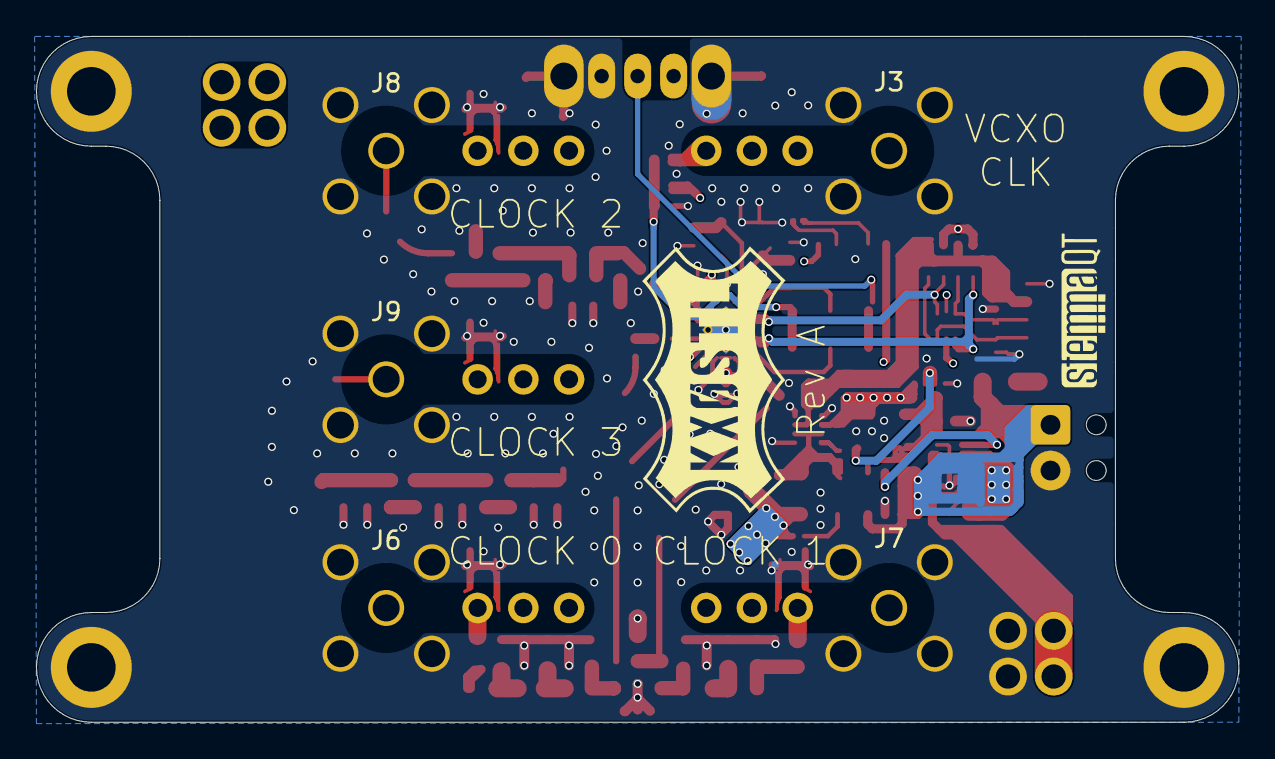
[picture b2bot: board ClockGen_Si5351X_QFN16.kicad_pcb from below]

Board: 4 copper layers, 66.8 x 38.1 mm, 113 parts (7 on the bottom side), 59 nets.

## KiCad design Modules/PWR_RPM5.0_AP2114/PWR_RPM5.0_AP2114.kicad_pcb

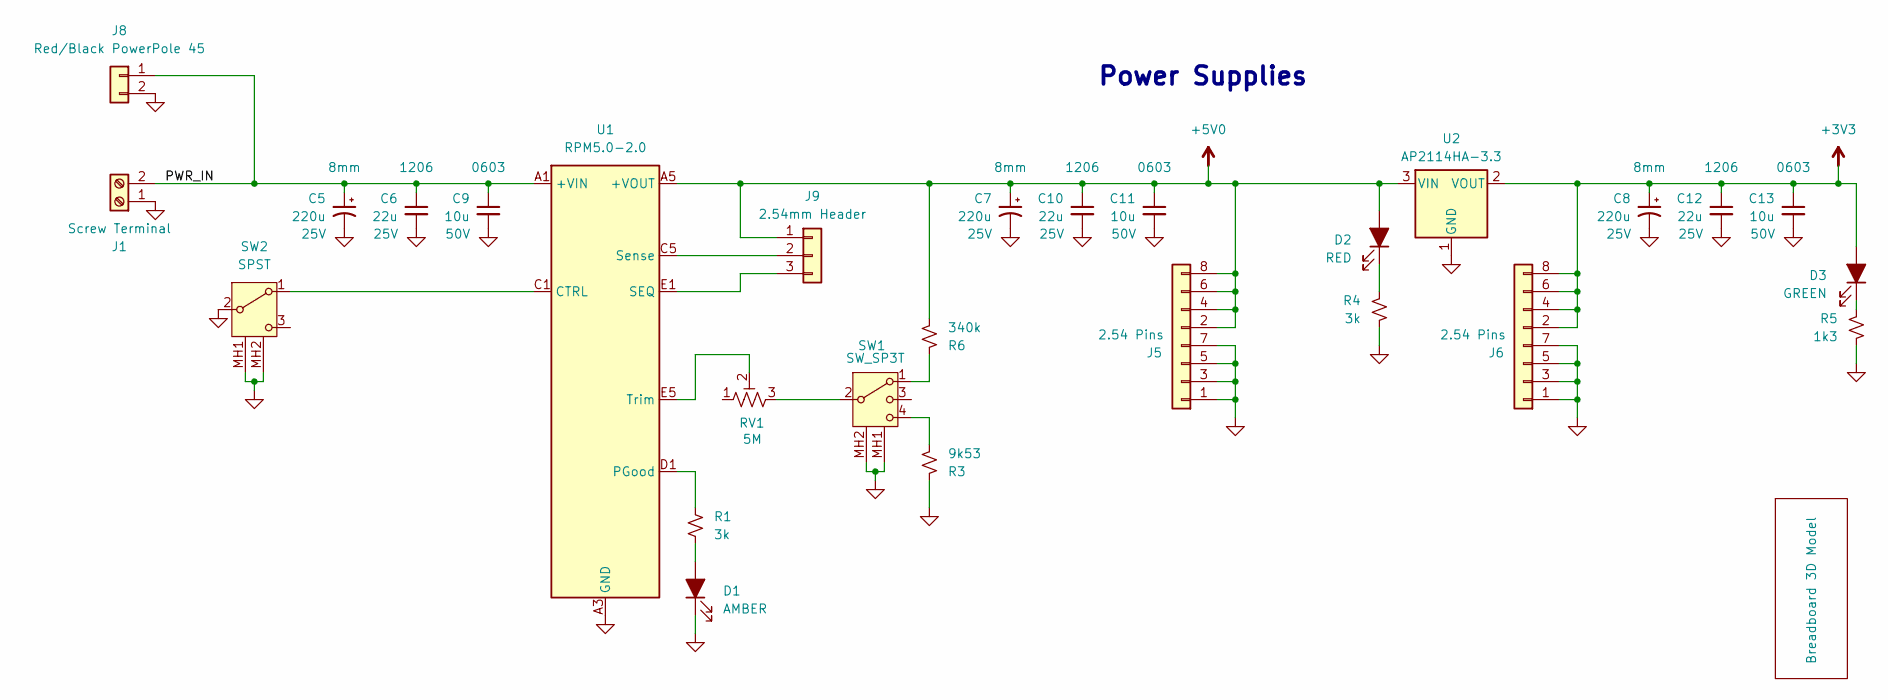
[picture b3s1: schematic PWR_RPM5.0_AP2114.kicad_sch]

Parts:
C5, C7, C8: 220u; CP_Radial_D6.3mm_P2.50mm; Voltage 25V; Manufacturer Part Number T491A336K010AT; DigiKey 399-5279-1-ND
C6, C10, C12: 22u; C_1206_3216Metric_Pad1.33x1.80mm_HandSolder; Voltage 25V; Part Number GMC31X5R226M25NT; DigiKey 4713-GMC31X5R226M25NTCT-ND
C9: 10u; C_0603_1608Metric; Voltage 50V; Part Number GMC10X5R106K25NT; DigiKey 4713-GMC10X5R106K25NTCT-ND
C11, C13: 10u; C_0603_1608Metric; Voltage 50V; Manufacturer Part Number GMC10X5R106K25NT; DigiKey 399-5279-1-ND
D1: AMBER; LED_D3.0mm; Part Number LTL-4291N; DigiKey 160-1968-ND
D2: RED; LED_D3.0mm; Part Number LLR3ED199G; DigiKey 5366-LLR3ED199G-ND
D3: GREEN; LED_D3.0mm; Part Number BL-BGE1V5D-AT; DigiKey BL-BGE1V5D-AT-ND
J1: Screw Terminal; TerminalBlock_Phoenix_MPT-0,5-2-2.54_1x02_P2.54mm_Horizontal; Part Number 1725656; DigiKey 277-1273-ND
J5, J6: 2.54 Pins; PinHeader_2x04_P2.54mm_Vertical
J8: Red/Black PowerPole 45; APP_ASMPR45-1X2-RK; Part Number ASMPR45-1X2-RK; DigiKey 2243-ASMPR45-1X2-RK-ND
J9: 2.54mm Header; PinHeader_1x03_P2.54mm_Vertical
R1, R4: 3k; R_0402_1005Metric; Part Number RM04F3001CT; DigiKey 4713-RM04F3001CT-ND
R3: 9k53; R_0402_1005Metric; Part Number RM04F9531CT; DigiKey 4713-RM04F9531CT-ND
R5: 1k3; R_0402_1005Metric; Part Number RM04F1301CT; DigiKey 4713-RM04F1301CT-ND
R6: 340k; R_0402_1005Metric; Part Number RM04F3403CT; DigiKey 4713-RM04F3403CT-ND
RV1: 5M; Potentiometer_Bourns_3299Y_Vertical; Part Number 3299Y-1-505LF; DigiKey 3299Y-505LF-ND
S1: Breadboard 3D Model; Breadboard_400
SW1: SW_SP3T; OS103011MA7QP1; Part Number OS103011MA7QP1; DigiKey CKN9561-ND
SW2: SPST; SW_Slide_SPDT_Angled_CK_OS102011MA1Q; Part Number OS102011MA1QN1; DigiKey CKN9559-ND
U1: RPM5.0-2.0; Converter_DCDC_RECOM_RPMx.x-x.0; Part Number RPM5.0-2.0-CT; DigiKey 945-3455-ND
U2: AP2114HA-3.3; SOT-223; Part Number AP2114HA-3.3TRG1; DigiKey AP2114HA-3.3TRG1DICT-ND

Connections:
+3V3: C8.1, C12.1, C13.1, D3.2 (A), J6.2, J6.4, J6.6, J6.8, U2.2 (VOUT)
+5V0: C7.1, C10.1, C11.1, D2.2 (A), J5.2, J5.4, J5.6, J5.8, J9.1, R6.2, U1.A5 (+VOUT), U1.B5 (+VOUT), U2.3 (VIN)
/PWR_IN: C5.1, C6.1, C9.1, J1.2, J8.1, U1.A1 (+VIN), U1.A2 (+VIN)
GND: C5.2, C6.2, C7.2, C8.2, C9.2, C10.2, C11.2, C12.2, C13.2, D1.1 (K), J1.1, J5.1, J5.3, J5.5, J5.7, J6.1, J6.3, J6.5, J6.7, J8.2, R3.1, R4.2, R5.2, SW1.MH1 (MH), SW1.MH2 (MH), SW2.2 (B), SW2.MH1, SW2.MH2, U1.A3 (GND), U1.A4 (GND), U1.B1 (GND), U1.B2 (GND), U1.B3 (GND), U1.B4 (GND), U1.C2 (GND), U1.C3 (GND), U1.C4 (GND), U1.D2 (GND), U1.D3 (GND), U1.D4 (GND), U1.D5 (GND), U1.E3 (GND), U1.E4 (GND), U2.1 (GND), U2.4 (GND)
unnamed: D1.2 (A), R1.2
unnamed: D2.1 (K), R4.1
unnamed: D3.1 (K), R5.1
unnamed: J9.2, U1.C5 (Sense)
unnamed: J9.3, U1.E1 (SEQ)
unnamed: R3.2, SW1.4
unnamed: R6.1, SW1.1
unnamed: RV1.3, SW1.2
unnamed: SW2.1 (A), U1.C1 (CTRL)
unnamed: R1.1, U1.D1 (PGood)
unnamed: RV1.2, U1.E5 (Trim)

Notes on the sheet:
Power Supplies
